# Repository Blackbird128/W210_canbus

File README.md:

# W210_canbus

Dedicated hardware interface for communication with the CAN-B network of a Mercedes-Benz W210 (W202 or W208)
The board is based on the MCP2515 CAN controller and the TJA1055 fault-tolerant transceiver, compatible with ISO 11898-3 low-speed CAN networks.

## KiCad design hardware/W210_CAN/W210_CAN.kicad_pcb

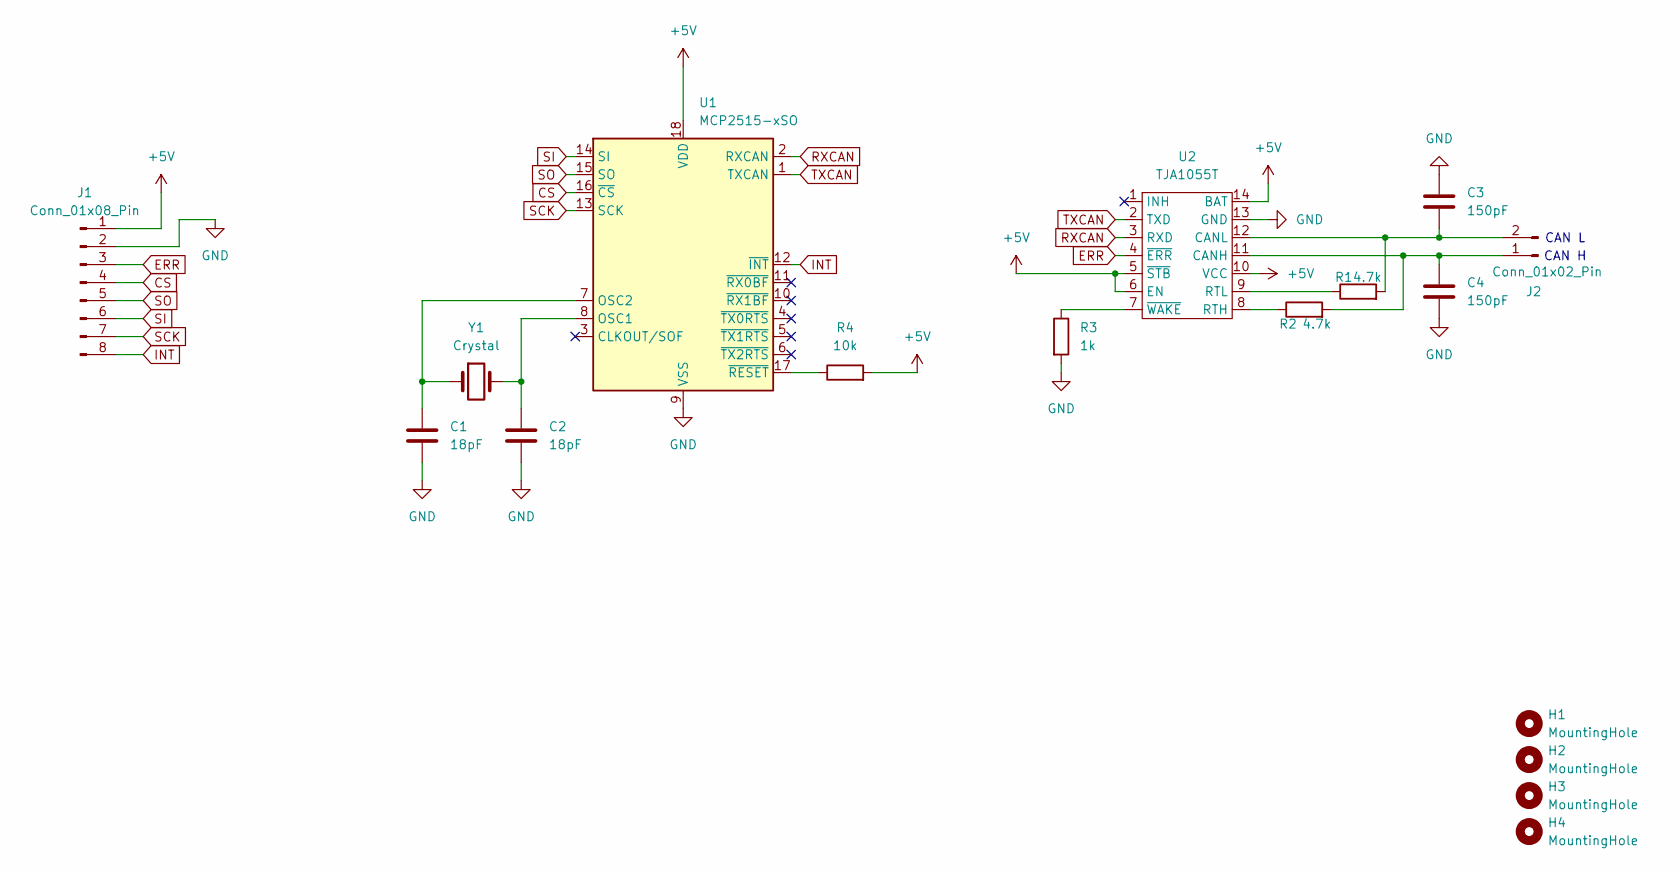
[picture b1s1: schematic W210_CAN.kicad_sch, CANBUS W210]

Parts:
C1, C2: 18pF; C_0805_2012Metric
C3, C4: 150pF; C_0805_2012Metric
H1, H2, H3, H4: MountingHole; MountingHole_2.2mm_M2
J1: Conn_01x08_Pin; PinSocket_1x08_P2.54mm_Vertical
J2: Conn_01x02_Pin; PinHeader_1x02_P2.54mm_Vertical
R1, R2: 4.7k; R_0805_2012Metric
R3: 1k; R_0805_2012Metric
R4: 10k; R_0805_2012Metric
U1: MCP2515-xSO; SOIC-18W_7.5x11.6mm_P1.27mm
U2: TJA1055T; SO-14_3.9x8.65mm_P1.27mm
Y1: Crystal; Crystal_HC49-4H_Vertical

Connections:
+5V: J1.1, R4.2, U1.18 (VDD), U2.5 (~STB), U2.6 (EN), U2.10 (VCC), U2.14 (BAT)
CS: J1.4, U1.16 (~CS)
ERR: J1.3, U2.4 (~ERR)
GND: C1.2, C2.2, C3.1, C4.2, J1.2, R3.2, U1.9 (VSS), U2.13 (GND)
INT: J1.8, U1.12 (~INT)
unnamed: C4.1, J2.1, R2.2, U2.11 (CANH)
unnamed: C3.2, J2.2, R1.2, U2.12 (CANL)
unnamed: C2.1, U1.8 (OSC1), Y1.2
unnamed: C1.1, U1.7 (OSC2), Y1.1
unnamed: R4.1, U1.17 (~RESET)
unnamed: R2.1, U2.8 (RTH)
unnamed: R1.1, U2.9 (RTL)
unnamed: R3.1, U2.7 (~WAKE)
RXCAN: U1.2 (RXCAN), U2.3 (RXD)
SCK: J1.7, U1.13 (SCK)
SI: J1.6, U1.14 (SI)
SO: J1.5, U1.15 (SO)
TXCAN: U1.1 (TXCAN), U2.2 (TXD)

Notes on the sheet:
CAN L
CAN H

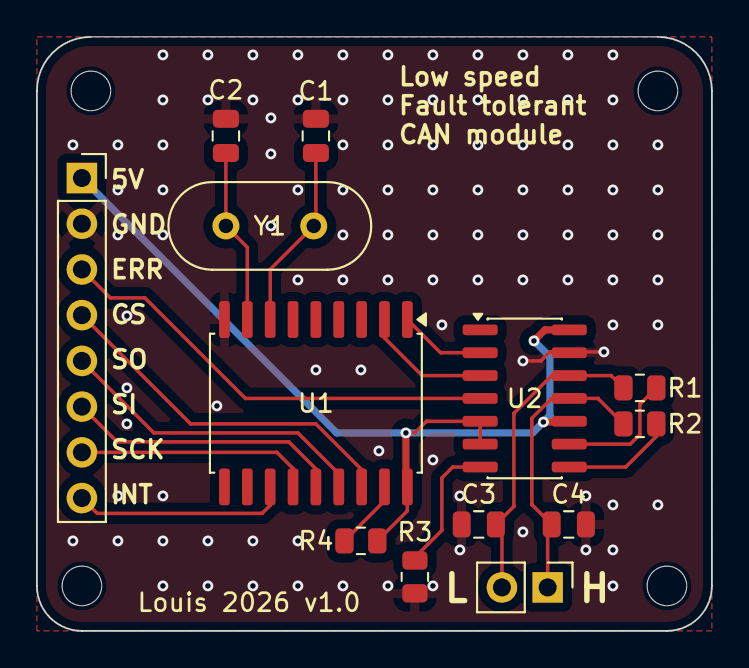
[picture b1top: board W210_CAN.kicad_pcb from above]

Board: 2 copper layers, 37.5 x 33.0 mm, 17 parts (0 on the bottom side), 18 nets.

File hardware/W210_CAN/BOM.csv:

"Reference","Qty","Value","DNP","Exclude from BOM","Exclude from Board","Footprint","Datasheet"
"C1,C2","2","18pF","","","","Capacitor_SMD:C_0805_2012Metric","~"
"C3,C4","2","150pF","","","","Capacitor_SMD:C_0805_2012Metric","~"
"H1,H2,H3,H4","4","MountingHole","","Exclure de la Liste du Matériel","","MountingHole:MountingHole_2.2mm_M2","~"
"J1","1","Conn_01x08_Pin","","","","Connector_PinSocket_2.54mm:PinSocket_1x08_P2.54mm_Vertical","~"
"J2","1","Conn_01x02_Pin","","","","Connector_PinHeader_2.54mm:PinHeader_1x02_P2.54mm_Vertical","~"
"R1,R2","2","4.7k","","","","Resistor_SMD:R_0805_2012Metric","~"
"R3","1","1k","","","","Resistor_SMD:R_0805_2012Metric","~"
"R4","1","10k","","","","Resistor_SMD:R_0805_2012Metric","~"
"U1","1","MCP2515-xSO","","","","Package_SO:SOIC-18W_7.5x11.6mm_P1.27mm","http://ww1.microchip.com/downloads/en/DeviceDoc/21801e.pdf"
"U2","1","TJA1055T","","","","Package_SO:SO-14_3.9x8.65mm_P1.27mm",""
"Y1","1","Crystal","","","","Crystal:Crystal_HC49-4H_Vertical","~"

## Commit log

2026-02-09 Add initial README
